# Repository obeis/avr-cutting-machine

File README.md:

## AVR Automatic Cutting Machine

### atmega32a

### build

```
cd src
make
make upload
```

				MOTOR_D - INT2
	MOTOR_A - INT0						MOTOR_B - INT1
				MOTOR_C (front vector) - INT2

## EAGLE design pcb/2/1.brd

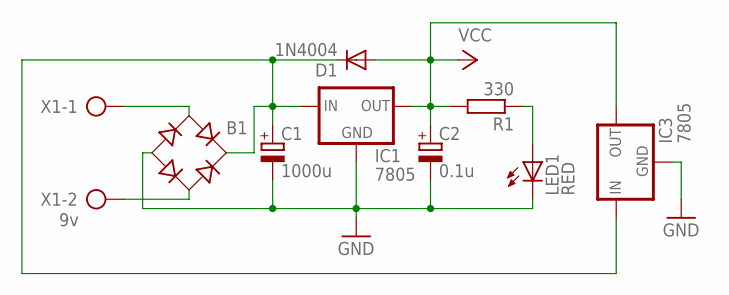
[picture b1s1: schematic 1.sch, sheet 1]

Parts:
B1: RB1A
C1: 1000u; E3,5-8
C2: 0.1u; E2-5
D1: 1N4004; DO41-10
IC1, IC3: 7805; 78XXS
LED1: RED; LED5MM
R1: 330; 0204/7
X1: 9v; AK500/2

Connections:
GND: B1.-, C1.-, C2.-, IC1.GND, IC3.GND, LED1.K (C); also elsewhere on the board
unnamed: B1.AC1, X1.1
unnamed: B1.AC2, X1.2
unnamed: B1.+, C1.+, D1.C, IC1.IN, IC3.IN
unnamed: LED1.A, R1.1
VCC: C2.+, D1.A, IC1.OUT, IC3.OUT, R1.2; also elsewhere on the board

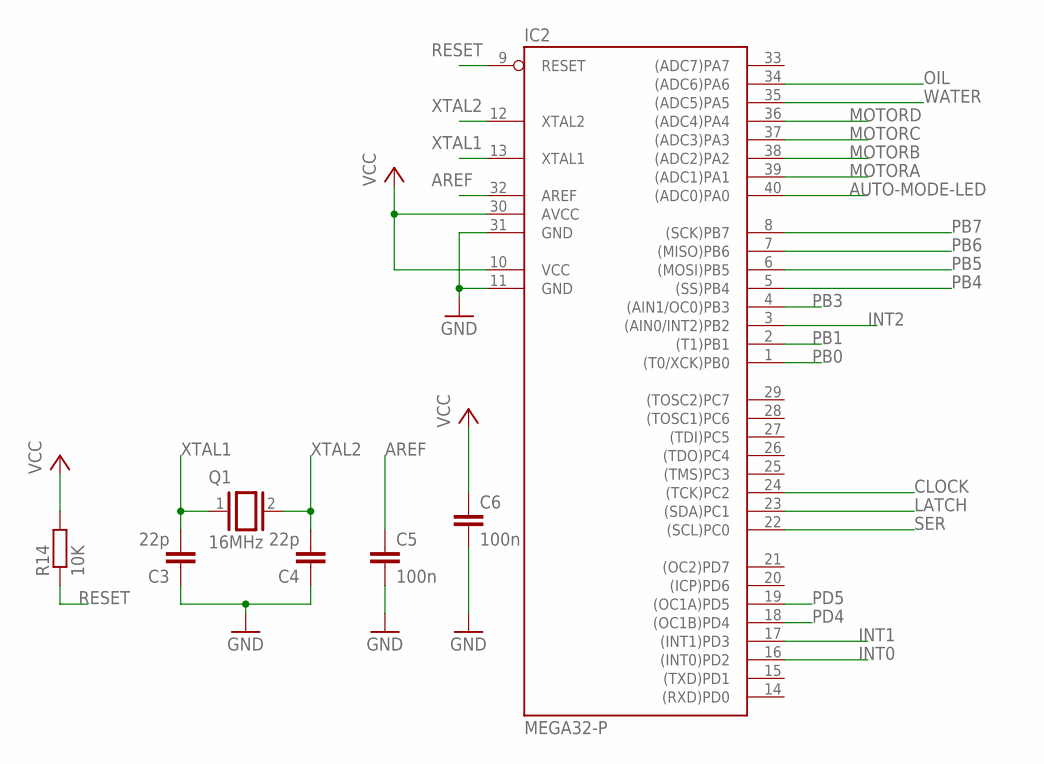
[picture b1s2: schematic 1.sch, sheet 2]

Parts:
C3, C4: 22p; C025-024X044
C5, C6: 100n; C025-024X044
IC2: MEGA32-P; DIL40
Q1: 16MHz; Q
R14: 10K; 0204/7

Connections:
AREF: C5.1, IC2.32 (AREF)
AUTO-MODE-LED: IC2.40 ((ADC0)PA0); also elsewhere on the board
CLOCK: IC2.24 ((TCK)PC2); also elsewhere on the board
GND: C3.1, C4.1, C5.2, C6.2, IC2.11 (GND), IC2.31 (GND); also elsewhere on the board
INT0: IC2.16 ((INT0)PD2); also elsewhere on the board
INT1: IC2.17 ((INT1)PD3); also elsewhere on the board
INT2: IC2.3 ((AIN0/INT2)PB2); also elsewhere on the board
LATCH: IC2.23 ((SDA)PC1); also elsewhere on the board
MOTORA: IC2.39 ((ADC1)PA1); also elsewhere on the board
MOTORB: IC2.38 ((ADC2)PA2); also elsewhere on the board
MOTORC: IC2.37 ((ADC3)PA3); also elsewhere on the board
MOTORD: IC2.36 ((ADC4)PA4); also elsewhere on the board
OIL: IC2.34 ((ADC6)PA6); also elsewhere on the board
PB0: IC2.1 ((T0/XCK)PB0); also elsewhere on the board
PB1: IC2.2 ((T1)PB1); also elsewhere on the board
PB3: IC2.4 ((AIN1/OC0)PB3); also elsewhere on the board
PB4: IC2.5 ((SS)PB4); also elsewhere on the board
PB5: IC2.6 ((MOSI)PB5); also elsewhere on the board
PB6: IC2.7 ((MISO)PB6); also elsewhere on the board
PB7: IC2.8 ((SCK)PB7); also elsewhere on the board
PD4: IC2.18 ((OC1B)PD4); also elsewhere on the board
PD5: IC2.19 ((OC1A)PD5); also elsewhere on the board
RESET: IC2.9 (RESET), R14.1; also elsewhere on the board
SER: IC2.22 ((SCL)PC0); also elsewhere on the board
VCC: C6.1, IC2.10 (VCC), IC2.30 (AVCC), R14.2; also elsewhere on the board
WATER: IC2.35 ((ADC5)PA5); also elsewhere on the board
XTAL1: C3.2, IC2.13 (XTAL1), Q1.1
XTAL2: C4.2, IC2.12 (XTAL2), Q1.2

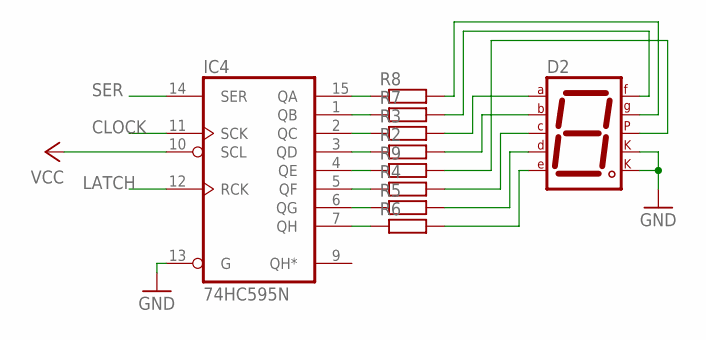
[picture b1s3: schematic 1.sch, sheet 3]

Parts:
D2: 7SEG-CK; 7SEG-13
IC4: 74HC595N; DIL16
R2, R3, R4, R5, R6, R7, R8, R9: R-EU_0204/7; 0204/7

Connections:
CLOCK: IC4.11 (SCK); also elsewhere on the board
GND: D2.3 (CK1), D2.8 (CK2), IC4.8 (GND), IC4.13 (G); also elsewhere on the board
LATCH: IC4.12 (RCK); also elsewhere on the board
unnamed: D2.7 (A), R3.2
unnamed: D2.6 (B), R2.2
unnamed: D2.9 (F), R7.2
unnamed: D2.2 (D), R5.2
unnamed: D2.1 (E), R6.2
unnamed: D2.10 (G), R8.2
unnamed: D2.5 (DP), R9.2
unnamed: IC4.15 (QA), R8.1
unnamed: IC4.4 (QE), R9.1
unnamed: IC4.1 (QB), R7.1
unnamed: IC4.2 (QC), R3.1
unnamed: IC4.3 (QD), R2.1
unnamed: IC4.5 (QF), R4.1
unnamed: IC4.6 (QG), R5.1
unnamed: IC4.7 (QH), R6.1
unnamed: D2.4 (C), R4.2
SER: IC4.14 (SER); also elsewhere on the board
VCC: IC4.10 (SCL), IC4.16 (VCC); also elsewhere on the board

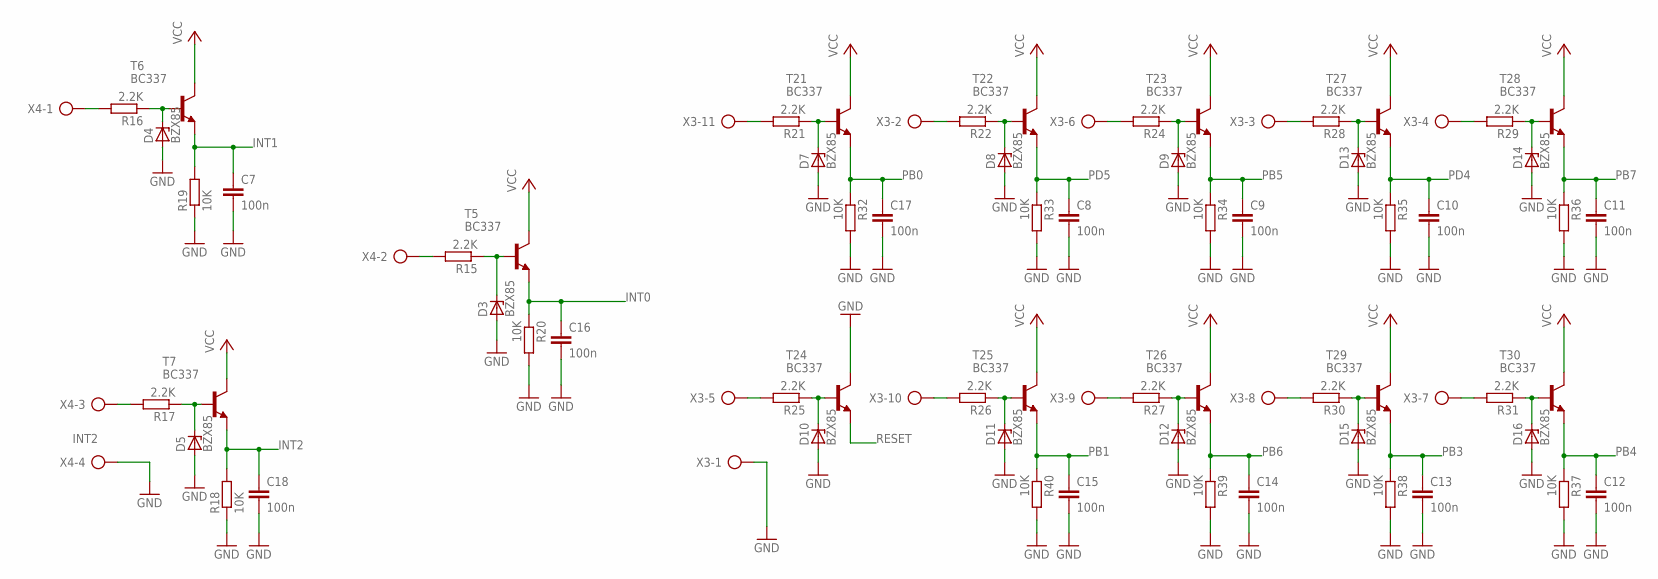
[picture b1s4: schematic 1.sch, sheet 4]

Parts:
C7, C8, C9, C10, C11, C12, C13, C14, C15, C16, C17, C18: 100n; C025-024X044
D3, D4, D5, D7, D8, D9, D10, D11, D12, D13, D14, D15, D16: BZX85; DO41Z10
R15, R16, R17, R21, R22, R24, R25, R26, R27, R28, R29, R30, R31: 2.2K; 0207/10
R18, R19, R20, R32, R33, R34, R35, R36, R37, R38, R39, R40: 10K; 0204/7
T5, T6, T7, T21, T22, T23, T24, T25, T26, T27, T28, T29, T30: BC337; TO92
X3: AK500/11
X4: AK500/4

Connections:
GND: C7.2, C8.2, C9.2, C10.2, C11.2, C12.2, C13.2, C14.2, C15.2, C16.2, C17.2, C18.2, D3.A, D4.A, D5.A, D7.A, D8.A, D9.A, D10.A, D11.A, D12.A, D13.A, D14.A, D15.A, D16.A, R18.1, R19.1, R20.2, R32.2, R33.2, R34.2, R35.2, R36.2, R37.2, R38.2, R39.2, R40.2, T24.3 (C), X3.1, X4.4; also elsewhere on the board
INT0: C16.1, R20.1, T5.1 (E); also elsewhere on the board
INT1: C7.1, R19.2, T6.1 (E); also elsewhere on the board
INT2: C18.1, R18.2, T7.1 (E); also elsewhere on the board
unnamed: R21.2, X3.11
unnamed: D7.C, R21.1, T21.2 (B)
unnamed: D8.C, R22.1, T22.2 (B)
unnamed: D9.C, R24.1, T23.2 (B)
unnamed: D10.C, R25.1, T24.2 (B)
unnamed: D11.C, R26.1, T25.2 (B)
unnamed: D12.C, R27.1, T26.2 (B)
unnamed: D3.C, R15.1, T5.2 (B)
unnamed: D5.C, R17.1, T7.2 (B)
unnamed: R16.2, X4.1
unnamed: R17.2, X4.3
unnamed: R15.2, X4.2
unnamed: D13.C, R28.1, T27.2 (B)
unnamed: D14.C, R29.1, T28.2 (B)
unnamed: D15.C, R30.1, T29.2 (B)
unnamed: D16.C, R31.1, T30.2 (B)
unnamed: R25.2, X3.5
unnamed: R26.2, X3.10
unnamed: R27.2, X3.9
unnamed: R30.2, X3.8
unnamed: R31.2, X3.7
unnamed: R29.2, X3.4
unnamed: R28.2, X3.3
unnamed: R24.2, X3.6
unnamed: R22.2, X3.2
unnamed: D4.C, R16.1, T6.2 (B)
PB0: C17.1, R32.1, T21.1 (E); also elsewhere on the board
PB1: C15.1, R40.1, T25.1 (E); also elsewhere on the board
PB3: C13.1, R38.1, T29.1 (E); also elsewhere on the board
PB4: C12.1, R37.1, T30.1 (E); also elsewhere on the board
PB5: C9.1, R34.1, T23.1 (E); also elsewhere on the board
PB6: C14.1, R39.1, T26.1 (E); also elsewhere on the board
PB7: C11.1, R36.1, T28.1 (E); also elsewhere on the board
PD4: C10.1, R35.1, T27.1 (E); also elsewhere on the board
PD5: C8.1, R33.1, T22.1 (E); also elsewhere on the board
RESET: T24.1 (E); also elsewhere on the board
VCC: T5.3 (C), T6.3 (C), T7.3 (C), T21.3 (C), T22.3 (C), T23.3 (C), T25.3 (C), T26.3 (C), T27.3 (C), T28.3 (C), T29.3 (C), T30.3 (C); also elsewhere on the board

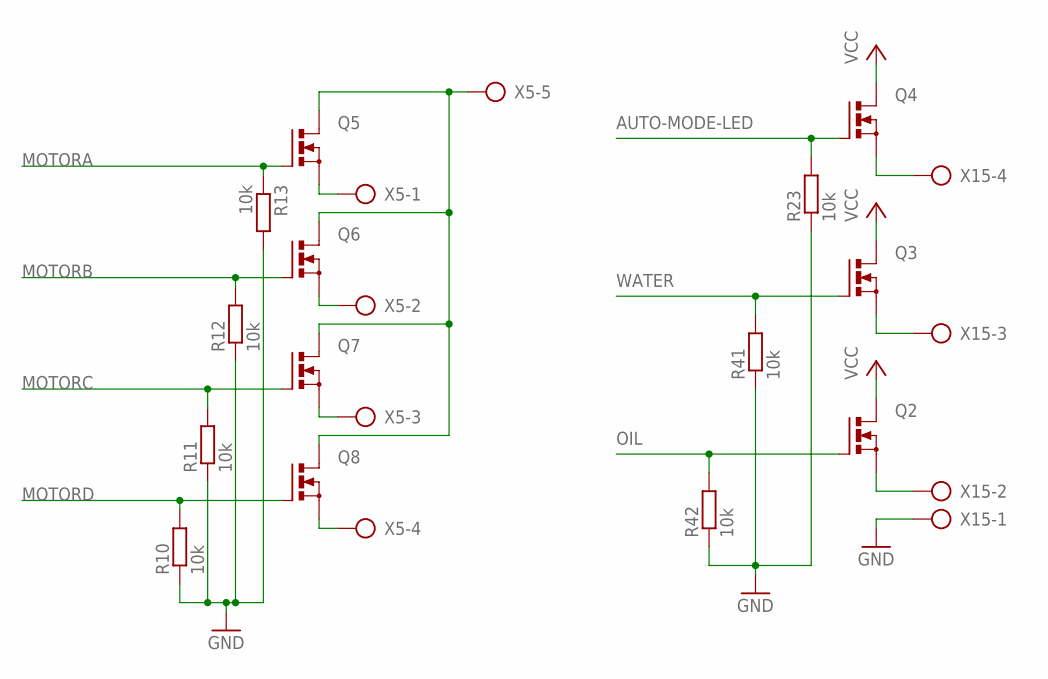
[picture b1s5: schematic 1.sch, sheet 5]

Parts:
Q2, Q3, Q4, Q5, Q6, Q7, Q8: N-MOSFET-SO8S; SO-08
R10, R11, R12, R13, R23, R41, R42: 10k; 0204/7
X5: AK500/5
X15: AK500/4

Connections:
AUTO-MODE-LED: Q4.4 (G), R23.2; also elsewhere on the board
GND: R10.1, R11.1, R12.1, R13.2, R23.1, R41.1, R42.1, X15.1; also elsewhere on the board
MOTORA: Q5.4 (G), R13.1; also elsewhere on the board
MOTORB: Q6.4 (G), R12.2; also elsewhere on the board
MOTORC: Q7.4 (G), R11.2; also elsewhere on the board
MOTORD: Q8.4 (G), R10.2; also elsewhere on the board
unnamed: Q5.1 (S), Q5.2 (S), Q5.3 (S), X5.1
unnamed: Q6.1 (S), Q6.2 (S), Q6.3 (S), X5.2
unnamed: Q7.1 (S), Q7.2 (S), Q7.3 (S), X5.3
unnamed: Q8.1 (S), Q8.2 (S), Q8.3 (S), X5.4
unnamed: Q4.1 (S), Q4.2 (S), Q4.3 (S), X15.4
unnamed: Q3.1 (S), Q3.2 (S), Q3.3 (S), X15.3
unnamed: Q2.1 (S), Q2.2 (S), Q2.3 (S), X15.2
unnamed: Q5.5 (D), Q5.6 (D), Q5.7 (D), Q5.8 (D), Q6.5 (D), Q6.6 (D), Q6.7 (D), Q6.8 (D), Q7.5 (D), Q7.6 (D), Q7.7 (D), Q7.8 (D), Q8.5 (D), Q8.6 (D), Q8.7 (D), Q8.8 (D), X5.5
OIL: Q2.4 (G), R42.2; also elsewhere on the board
VCC: Q2.5 (D), Q2.6 (D), Q2.7 (D), Q2.8 (D), Q3.5 (D), Q3.6 (D), Q3.7 (D), Q3.8 (D), Q4.5 (D), Q4.6 (D), Q4.7 (D), Q4.8 (D); also elsewhere on the board
WATER: Q3.4 (G), R41.2; also elsewhere on the board

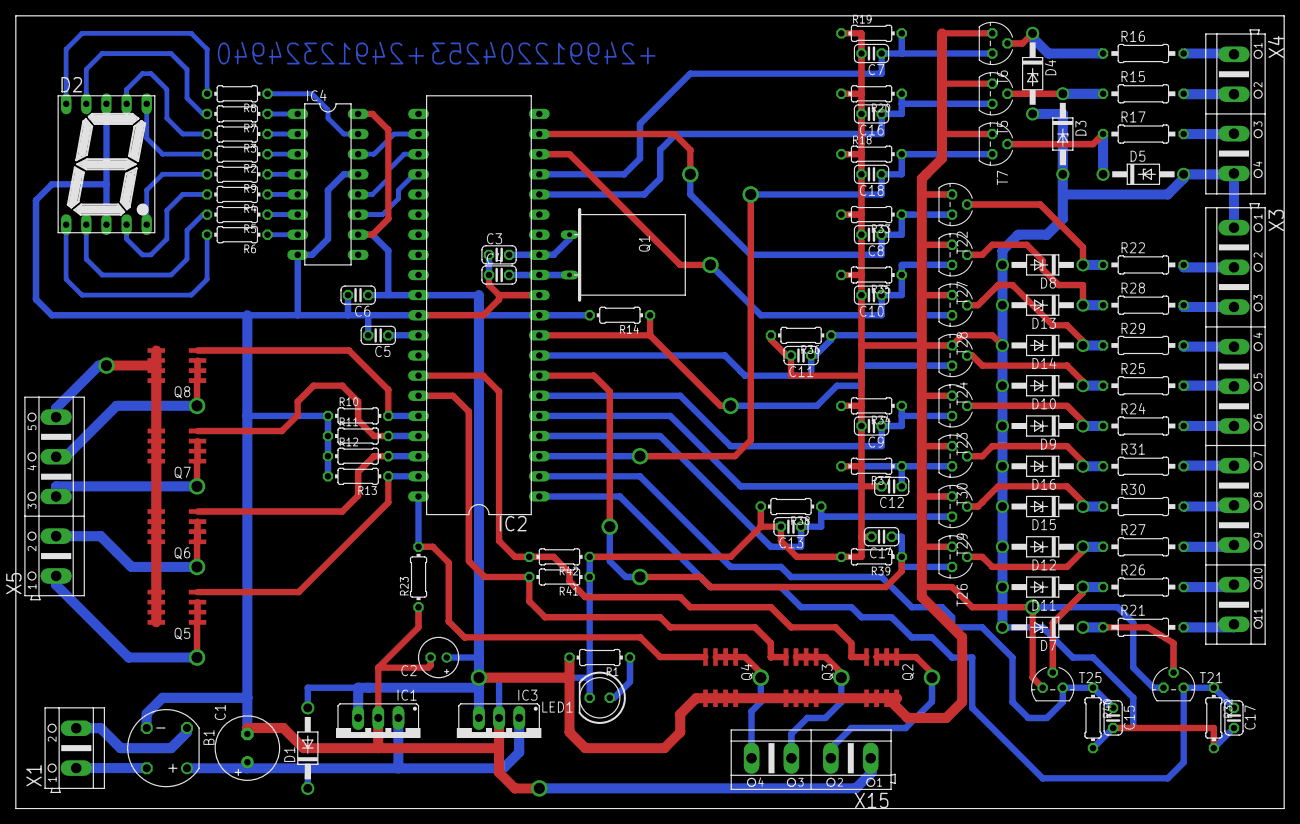
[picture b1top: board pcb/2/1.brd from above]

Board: 2 copper layers, 160.0 x 100.0 mm, 107 parts (0 on the bottom side), 82 nets.

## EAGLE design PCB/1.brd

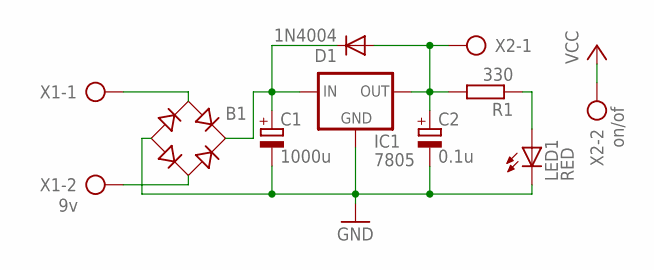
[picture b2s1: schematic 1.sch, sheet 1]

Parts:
B1: RB1A
C1: 1000u; E3,5-8
C2: 0.1u; E2-5
D1: 1N4004; DO41-10
IC1: 7805; 78XXS
LED1: RED; LED5MM
R1: 330; 0204/7
X1: 9v; AK500/2
X2: on/of; AK500/2

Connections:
GND: B1.-, C1.-, C2.-, IC1.GND, LED1.K (C); also elsewhere on the board
unnamed: B1.AC1, X1.1
unnamed: B1.AC2, X1.2
unnamed: B1.+, C1.+, D1.C, IC1.IN
unnamed: LED1.A, R1.1
unnamed: C2.+, D1.A, IC1.OUT, R1.2, X2.1
VCC: X2.2; also elsewhere on the board

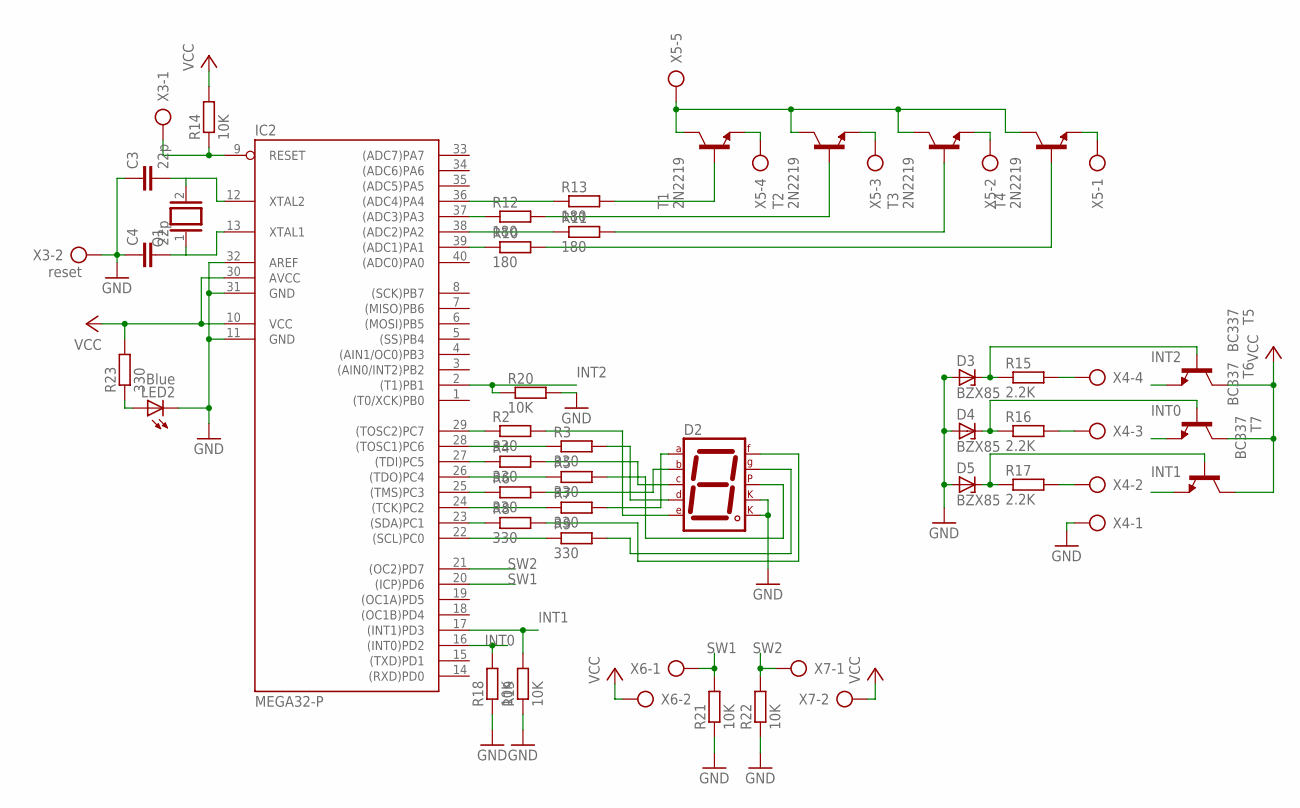
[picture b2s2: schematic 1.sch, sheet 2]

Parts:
C3, C4: 22p; C025-024X044
D2: 7SEG-CK; 7SEG-13
D3, D4, D5: BZX85; DO41Z10
IC2: MEGA32-P; DIL40
LED2: Blue; LED5MM
Q1: XTAL; Q
R2, R3, R4, R5, R6, R7, R8, R9, R23: 330; 0204/7
R10, R11, R12, R13: 180; 0204/7
R14, R18, R19, R20, R21, R22: 10K; 0204/7
R15, R16, R17: 2.2K; 0207/10
T1, T2, T3, T4: 2N2219; TO5
T5, T6, T7: BC337; TO92
X3: reset; AK500/2
X4: AK500/4
X5: AK500/5
X6, X7: AK500/2

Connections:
GND: C3.1, C4.1, D2.3 (CK1), D2.8 (CK2), D3.A, D4.A, D5.A, IC2.11 (GND), IC2.31 (GND), IC2.32 (AREF), LED2.K (C), R18.1, R19.1, R20.2, R21.1, R22.1, X3.2, X4.1; also elsewhere on the board
INT0: IC2.16 ((INT0)PD2), R18.2, T6.1 (E)
INT1: IC2.17 ((INT1)PD3), R19.2, T7.1 (E)
INT2: IC2.2 ((T1)PB1), R20.1, T5.1 (E)
unnamed: D2.1 (E), R2.2
unnamed: D2.2 (D), R3.2
unnamed: D2.4 (C), R4.2
unnamed: D2.5 (DP), R5.2
unnamed: D2.6 (B), R6.2
unnamed: D2.7 (A), R7.2
unnamed: D2.9 (F), R8.2
unnamed: D2.10 (G), R9.2
unnamed: IC2.29 ((TOSC2)PC7), R2.1
unnamed: IC2.28 ((TOSC1)PC6), R3.1
unnamed: IC2.27 ((TDI)PC5), R4.1
unnamed: IC2.26 ((TDO)PC4), R5.1
unnamed: IC2.25 ((TMS)PC3), R6.1
unnamed: IC2.24 ((TCK)PC2), R7.1
unnamed: IC2.23 ((SDA)PC1), R8.1
unnamed: IC2.22 ((SCL)PC0), R9.1
unnamed: IC2.39 ((ADC1)PA1), R10.1
unnamed: IC2.38 ((ADC2)PA2), R11.1
unnamed: IC2.37 ((ADC3)PA3), R12.1
unnamed: IC2.36 ((ADC4)PA4), R13.1
unnamed: LED2.A, R23.1
unnamed: C3.2, IC2.12 (XTAL2), Q1.2
unnamed: C4.2, IC2.13 (XTAL1), Q1.1
unnamed: IC2.9 (RESET), R14.1, X3.1
unnamed: D3.C, R15.1, T5.2 (B)
unnamed: D4.C, R16.1, T6.2 (B)
unnamed: D5.C, R17.1, T7.2 (B)
unnamed: R15.2, X4.4
unnamed: R16.2, X4.3
unnamed: R17.2, X4.2
unnamed: R12.2, T2.2 (B)
unnamed: R13.2, T1.2 (B)
unnamed: R11.2, T3.2 (B)
unnamed: R10.2, T4.2 (B)
unnamed: T1.3 (C), T2.3 (C), T3.3 (C), T4.3 (C), X5.5
unnamed: T1.1 (E), X5.4
unnamed: T2.1 (E), X5.3
unnamed: T3.1 (E), X5.2
unnamed: T4.1 (E), X5.1
SW1: IC2.20 ((ICP)PD6), R21.2, X6.1
SW2: IC2.21 ((OC2)PD7), R22.2, X7.1
VCC: IC2.10 (VCC), IC2.30 (AVCC), R14.2, R23.2, T5.3 (C), T6.3 (C), T7.3 (C), X6.2, X7.2; also elsewhere on the board

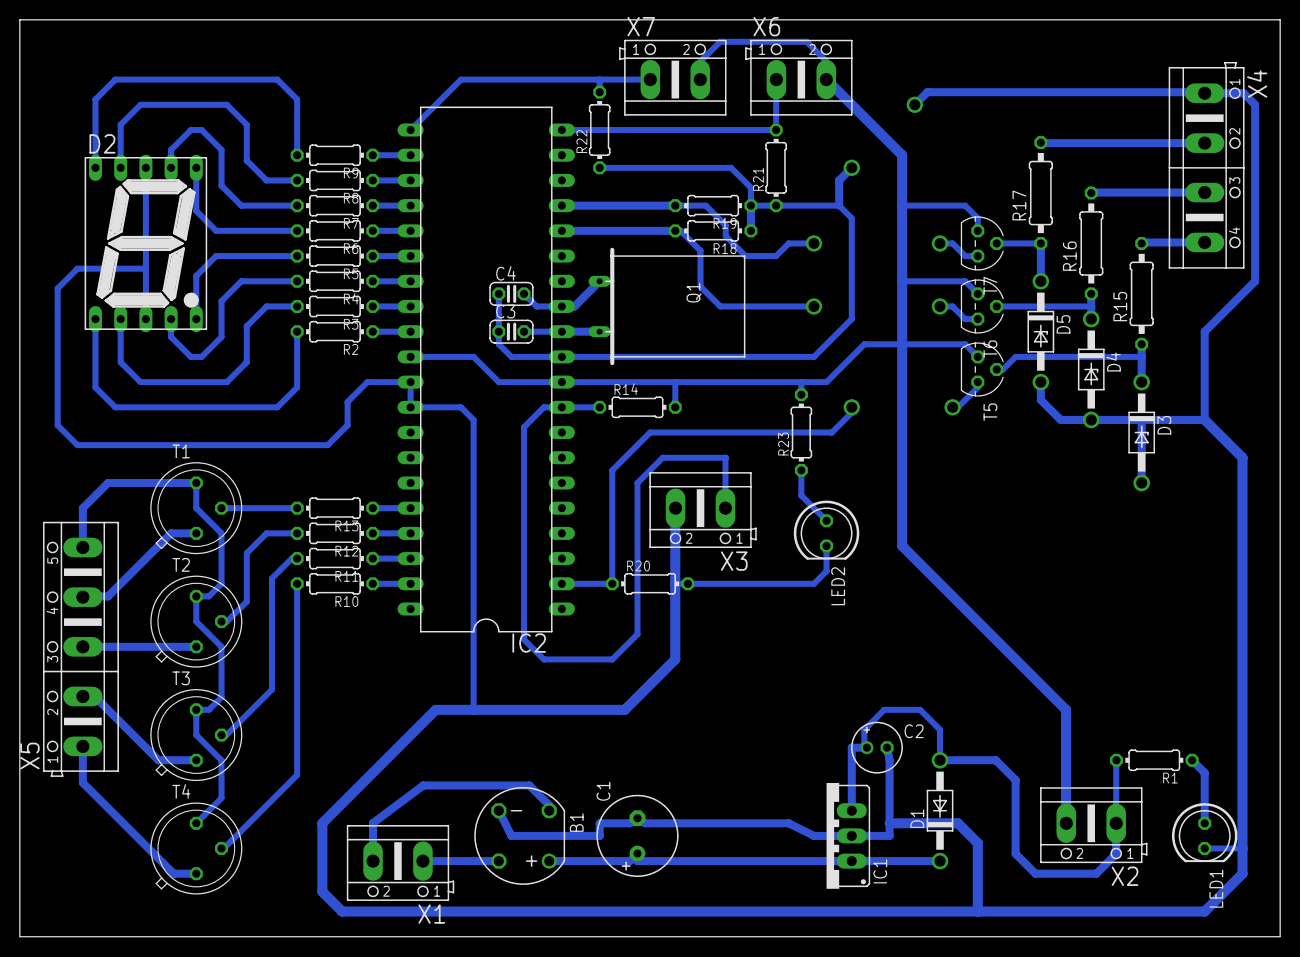
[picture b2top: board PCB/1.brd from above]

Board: 2 copper layers, 127.0 x 92.4 mm, 52 parts (0 on the bottom side), 51 nets.

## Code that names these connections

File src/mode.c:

#include <avr/io.h>
#include <util/delay.h>
#include "int.h"
#include "timer.h"
#include "motor.h"

uint8_t mode = 0;
/*
	0 = manual mode
	1 = auto mode
*/

/*
	* programming mode swith
        PD6 = programming mode start switch
        PD7 = change time switch

	* manual control switch
        PD0 = motor A (PA1)
        PD1 = motor B (PA2)
        PD4 = motor C (PA3)
        PD5 = motor D (PA4)

        PB0 = water (PA5)
        PB1 = oil (PA6)
        PB3 = auto start switch
	PA0 = auto mode LED
*/

void port_init()
{
	DDRA |= (1<<PA0) | (1<<PA6) | (1<<PA5);

	DDRB &= ~(1<<PB0);
	DDRB &= ~(1<<PB1);

	DDRD &=~ (1<<PD0);
	DDRD &=~ (1<<PD1);
	DDRD &=~ (1<<PD4);
	DDRD &=~ (1<<PD5);
	DDRD &=~ (1<<PD6);
	DDRD &=~ (1<<PD7);
}

void auto_mode_init()
{
	mode = 1;

	int_init();

	timer_0_1_enable();

	// led on
	PORTA |= (1<<PA0);

	motor_A_on();
}

void manual_mode_init()
{
	mode = 0;

	int_disable();

	timer_0_1_disble();

	motor_all_stop();

	// led off
        PORTA &= ~(1<<PA0);
}

void manual_mode()
{
	// manual control switch
	if(PIND & (1<<PD0))
	{
		motor_all_stop();
		motor_A_on();
        }
	else
		motor_A_off();

        if(PIND & (1<<PD1))
        {
		motor_all_stop();
		motor_B_on();
        }
	else
		motor_B_off();

        if(PIND & (1<<PD4))
        {
		motor_all_stop();
		motor_C_on();
        }
	else
		motor_C_off();

        if(PIND & (1<<PD5))
        {
		motor_all_stop();
		motor_D_on();
        }
	else
		motor_D_off();
}

void auto_mode()
{

}

void scan_switch()
{
	if(PINB & (1<<PB0))
        {
                PORTA ^= (1<<PA5);
		_delay_ms(350);
        }

        if(PINB & (1<<PB1))
        {
                PORTA ^= (1<<PA6);
		_delay_ms(350);
        }
}

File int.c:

#include <avr/io.h>
#include "int.h"

void int_init()
{
	// INT0 (PD2), INT1(PD3), INT(PB2) input
	DDRD |= (1<<PD2) | (1<<PD3);
	DDRB |= (1<<PB2);

	// rising edge of INT0,1,2
	MCUCR |= (1<<ISC11) | (1<<ISC10) | (1<<ISC01) | (1<<ISC00);
	MCUCSR |= (1<<ISC2);

	// INT1 INT0 INT2 interrupt enable
	GICR |= (1<<INT1) | (1<<INT0) | (1<<INT2);
}

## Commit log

2019-11-24 Test EEPROM
2019-11-24 Test interrupt
2019-11-24 Remove eeprom.c and eeprom.h
2019-11-24 Add fuse command to Makefile
2019-11-24 Create PCB
2019-11-24 Callig cli() function before stop all motor
    when switching to programming mode
2019-11-24 v0.9.1-rc3
2019-11-24 Edit INT2 interrupt
2019-11-24 7segment display is running by timer 2
2019-11-24 Fix PCB (PCB is working)
2019-11-24 Edit the default value of EEPROM
2019-11-24 Add manual mode and auto mode
2019-11-24 Add programming mode
2019-11-24 Fix PCB
2019-11-24 Test 7segment Display
2019-11-24 Add motor library
2019-11-24 Edit timer and PCB
2023-03-04 Edit readme
